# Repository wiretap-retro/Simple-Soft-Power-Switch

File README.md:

# Simple Soft Power Switch
A circuit for providing a power switch that latches, utilizing a momentary push button.

## Intro
This is a simple soft power switch that latches, using a momentary push button. It is found in many different devices from kids toys to consumer power supplies. I took apart an old electronic basketball hoop toy of my son's to reverse engineer the power switch circuit. This circuit is cheap and simple, costing less than a bottle of Coke. From the datasheet, it can handle 5-18VDC with approximately 4 amps of current. This is a neat design to use in small projects where you want a momentary push button for powering on and off your device. This does not do voltage step-up/step-down. What you feed into the power header is what comes out on the load side.

## Assembly / Install
* If used, the provided circuit board can be ordered from a PCB fabricator of your choice. (JLCPCB, PCBway, OSH Park, etc.)
* The components can be found from a wide variety of retailers. (Mouser, Digikey, RS, etc.)
* Solder the SMD components first. Pay attention to the orientation of the IRF7319.
* Solder the pin headers.
* Hook up a momentary switch to the SWITCH header.
* Hook up 5VDC to 18VDC to the PWR header.
* Hook up the device you want to power to the LOAD header.
* Press the momentary button once and your device turns on. Press it again and the device turns off.

## Important Note
With the provided PCB design with the small pin headers, use only low power IoT type devices. Don't melt your wiring and start a fire. This circuit is more intended to be used as an integration into other projects where you need a switched load.

## Misc
This project is open source. Feel free to do what you want with it.

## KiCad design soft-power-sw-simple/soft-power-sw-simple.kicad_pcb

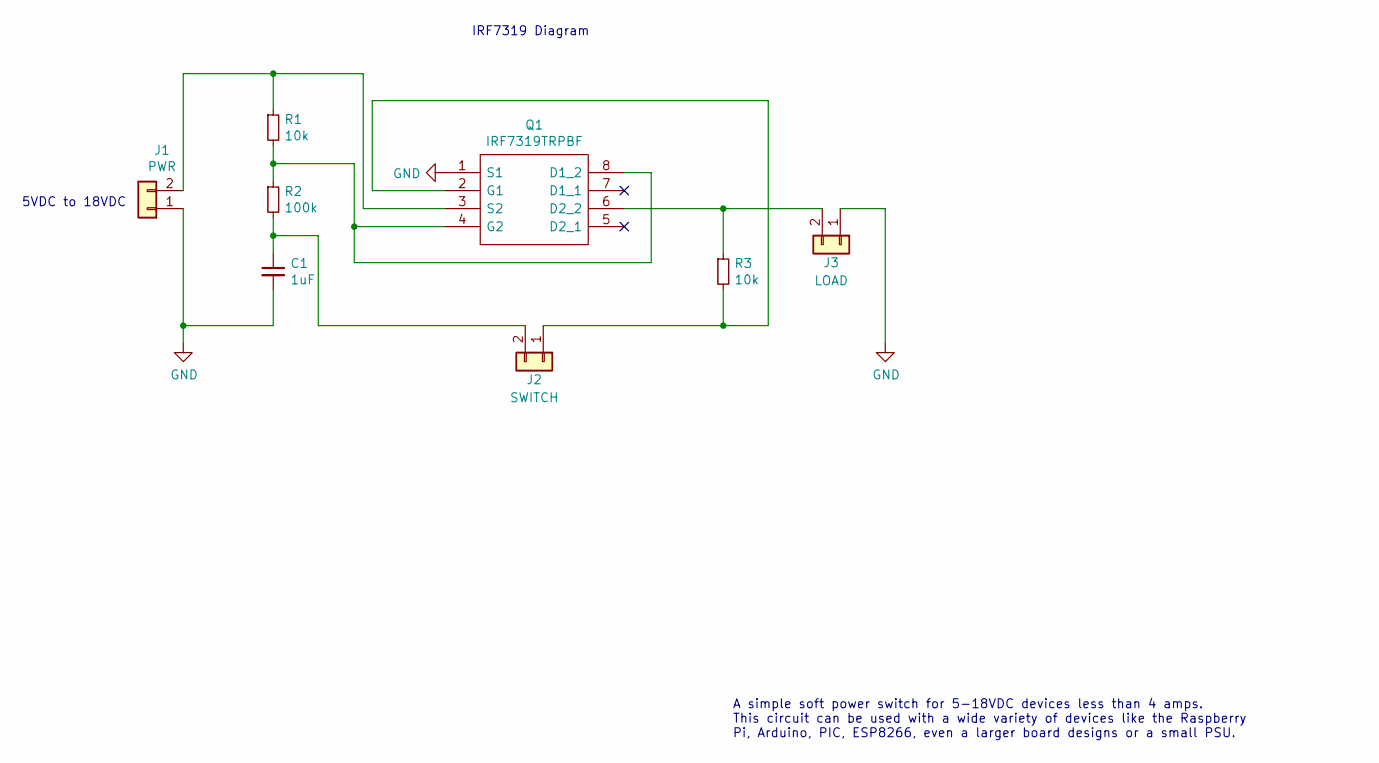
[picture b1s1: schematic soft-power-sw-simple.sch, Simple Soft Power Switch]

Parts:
C1: 1uF; C_0805_2012Metric_Pad1.15x1.40mm_HandSolder
J1: PWR; PinHeader_1x02_P2.54mm_Vertical
J2: SWITCH; PinHeader_1x02_P2.54mm_Vertical
J3: LOAD; PinHeader_1x02_P2.54mm_Vertical
Q1: IRF7319TRPBF; SOIC127P600X175-8N; Mouser Part Number 942-IRF7319TRPBF
R1, R3: 10k; R_0805_2012Metric_Pad1.15x1.40mm_HandSolder
R2: 100k; R_0805_2012Metric_Pad1.15x1.40mm_HandSolder

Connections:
GND: C1.2, J1.1, J3.1, Q1.1 (S1)
unnamed: C1.1, J2.2, R2.2
unnamed: J1.2, Q1.3 (S2), R1.1
unnamed: J2.1, Q1.2 (G1), R3.2
unnamed: J3.2, Q1.6 (D2_2), R3.1
unnamed: Q1.4 (G2), Q1.8 (D1_2), R1.2, R2.1

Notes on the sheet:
IRF7319 Diagram
5VDC to 18VDC
A simple soft power switch for 5-18VDC devices less than 4 amps. This circuit can be used with a wide variety of devices like the Raspberry Pi, Arduino, PIC, ESP8266, even a larger board designs or a small PSU.

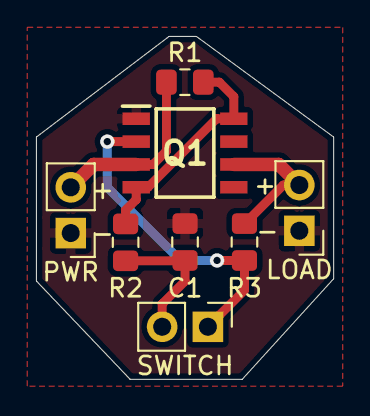
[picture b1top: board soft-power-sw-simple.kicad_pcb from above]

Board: 2 copper layers, 16.5 x 19.0 mm, 8 parts (0 on the bottom side), 6 nets.

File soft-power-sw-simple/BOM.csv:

Reference, Value, Footprint, Manufacturer_Name, Manufacturer_Part_Number, Mouser Part Number
C1,1uF,Capacitor_SMD:C_0805_2012Metric_Pad1.15x1.40mm_HandSolder,,,
J1,PWR,Connector_PinHeader_2.54mm:PinHeader_1x02_P2.54mm_Vertical,,,
J2,SWITCH,Connector_PinHeader_2.54mm:PinHeader_1x02_P2.54mm_Vertical,,,
J3,LOAD,Connector_PinHeader_2.54mm:PinHeader_1x02_P2.54mm_Vertical,,,
Q1,IRF7319TRPBF,SOIC127P600X175-8N,Infineon,IRF7319TRPBF,942-IRF7319TRPBF
R1,10k,Resistor_SMD:R_0805_2012Metric_Pad1.15x1.40mm_HandSolder,,,
R2,100k,Resistor_SMD:R_0805_2012Metric_Pad1.15x1.40mm_HandSolder,,,
R3,10k,Resistor_SMD:R_0805_2012Metric_Pad1.15x1.40mm_HandSolder,,,
